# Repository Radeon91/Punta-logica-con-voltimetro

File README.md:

# Punta-logica-con-voltimetro
Se trata de un proyecto de clase, es una punta logica con voltimetro incorporado, capaz de medir hasta 33v

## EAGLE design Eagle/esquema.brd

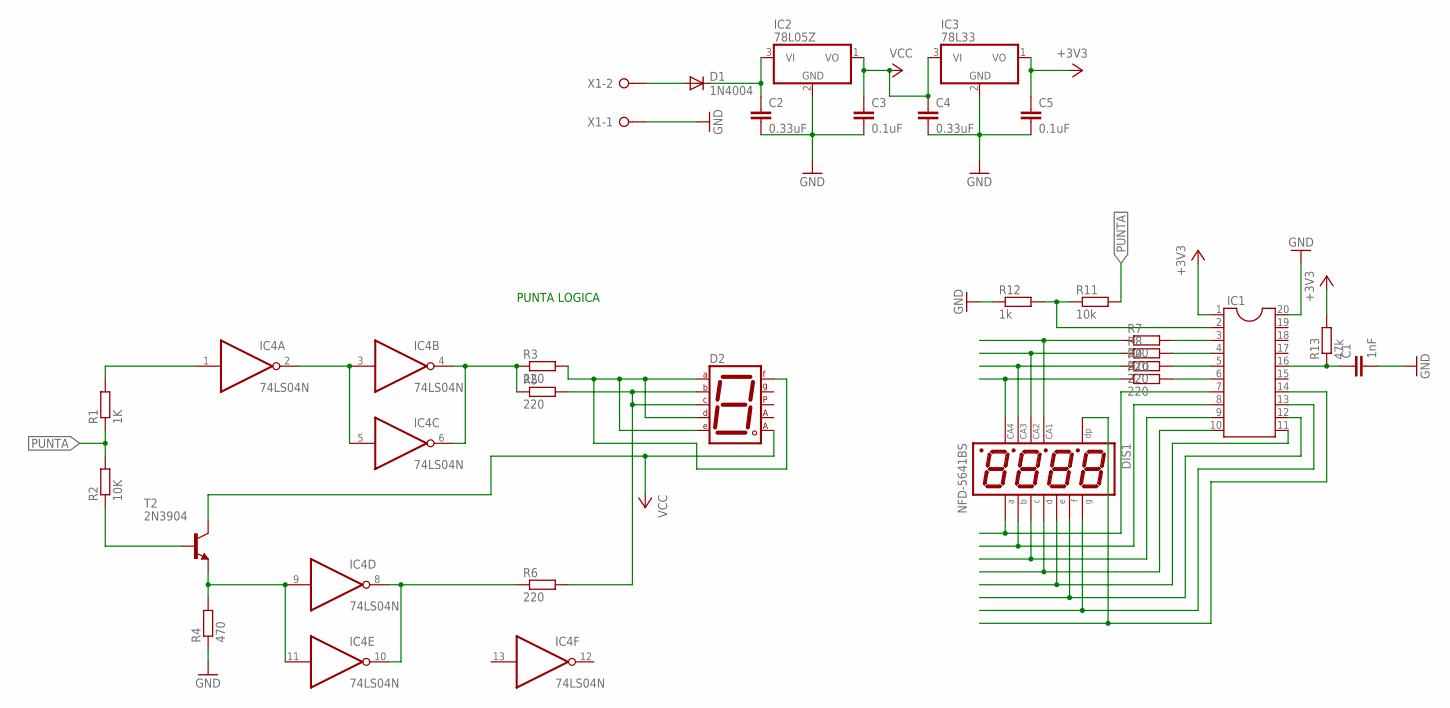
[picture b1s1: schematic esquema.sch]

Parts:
C1: 1nF; C050-024X044
C2, C4: 0.33uF; C050-024X044
C3, C5: 0.1uF; C050-024X044
D1: 1N4004; DO41-10
D2: 7SEG-CA; 7SEG-13
DIS1: NFD-5641BS; NFD-5641
IC1: DIL20S; SOCKET-20
IC2: 78L05Z; TO92
IC3: 78L33; TO92
IC4: 74LS04N; DIL14
R1: 1K; 0207/7
R2: 10K; 0207/7
R3, R5, R6, R7, R8, R9, R10: 220; 0207/7
R4: 470; 0207/7
R11: 10k; 0207/7
R12: 1k; 0207/7
R13: 47k; 0207/7
T2: 2N3904; TO92
X1: W237-02P; W237-132

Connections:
+3V3: C5.1, IC1.1, IC3.1 (VO), R13.2
GND: C1.2, C2.2, C3.2, C4.2, C5.2, IC1.20, IC2.2 (GND), IC3.2 (GND), IC4.7 (GND), R4.1, R12.1, X1.1
unnamed: C1.1, IC1.16, R13.1
unnamed: IC1.6, R10.2
unnamed: IC1.5, R9.2
unnamed: IC1.4, R8.2
unnamed: IC1.3, R7.2
unnamed: IC1.2, R11.1, R12.2
unnamed: DIS1.P$12, R7.1
unnamed: DIS1.P$9, R8.1
unnamed: DIS1.P$8, R9.1
unnamed: IC4.1 (I), R1.2
unnamed: IC4.2 (O), IC4.3 (I), IC4.5 (I)
unnamed: IC4.4 (O), IC4.6 (O), R3.1, R5.1
unnamed: R2.1, T2.2 (B)
unnamed: IC4.9 (I), IC4.11 (I), R4.2, T2.3 (E)
unnamed: D2.1 (E), D2.2 (D), D2.7 (A), D2.9 (F), R3.2
unnamed: IC4.8 (O), IC4.10 (O), R6.1
unnamed: D2.4 (C), D2.6 (B), R5.2, R6.2
unnamed: DIS1.P$6, R10.1
unnamed: DIS1.P$11, IC1.7
unnamed: DIS1.P$7, IC1.8
unnamed: DIS1.P$4, IC1.9
unnamed: DIS1.P$2, IC1.10
unnamed: DIS1.P$1, IC1.11
unnamed: DIS1.P$10, IC1.12
unnamed: DIS1.P$5, IC1.13
unnamed: DIS1.P$3, IC1.14
unnamed: D1.A, X1.2
unnamed: C2.1, D1.C, IC2.3 (VI)
PUNTA: R1.1, R2.2, R11.2
VCC: C3.1, C4.1, D2.8 (CA2), IC2.1 (VO), IC3.3 (VI), IC4.14 (VCC), T2.1 (C)

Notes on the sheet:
PUNTA LOGICA

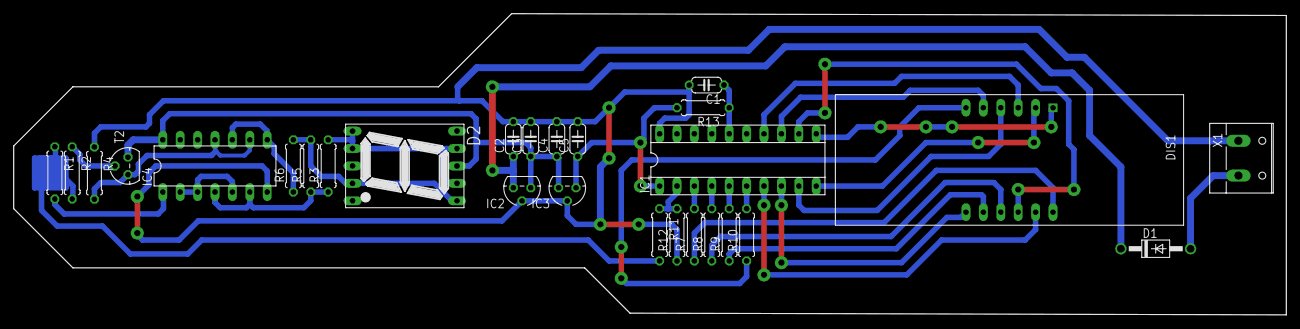
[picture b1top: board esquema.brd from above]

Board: 2 copper layers, 185.7 x 43.9 mm, 27 parts (0 on the bottom side), 32 nets.

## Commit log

2018-12-19 Create dsd
2018-12-19 Create Eagle
2018-12-19 Create df
2018-12-19 Create Altium
2018-12-19 Create ggj
